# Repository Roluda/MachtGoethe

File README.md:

# MachtGoethe
Arduino Sketche und Schaltpläne für "Escape the Library"

Die Grundstruktur des Buches ist im Buch_Schaltplan.pdf abgebildet.

Mehr Details zu spezifischen Rätseln finden sich in den "schemes" Ordnern der Rätsel.

Die Sketche für die Arduinos sind in den "firmware" Ordnern zu finden.

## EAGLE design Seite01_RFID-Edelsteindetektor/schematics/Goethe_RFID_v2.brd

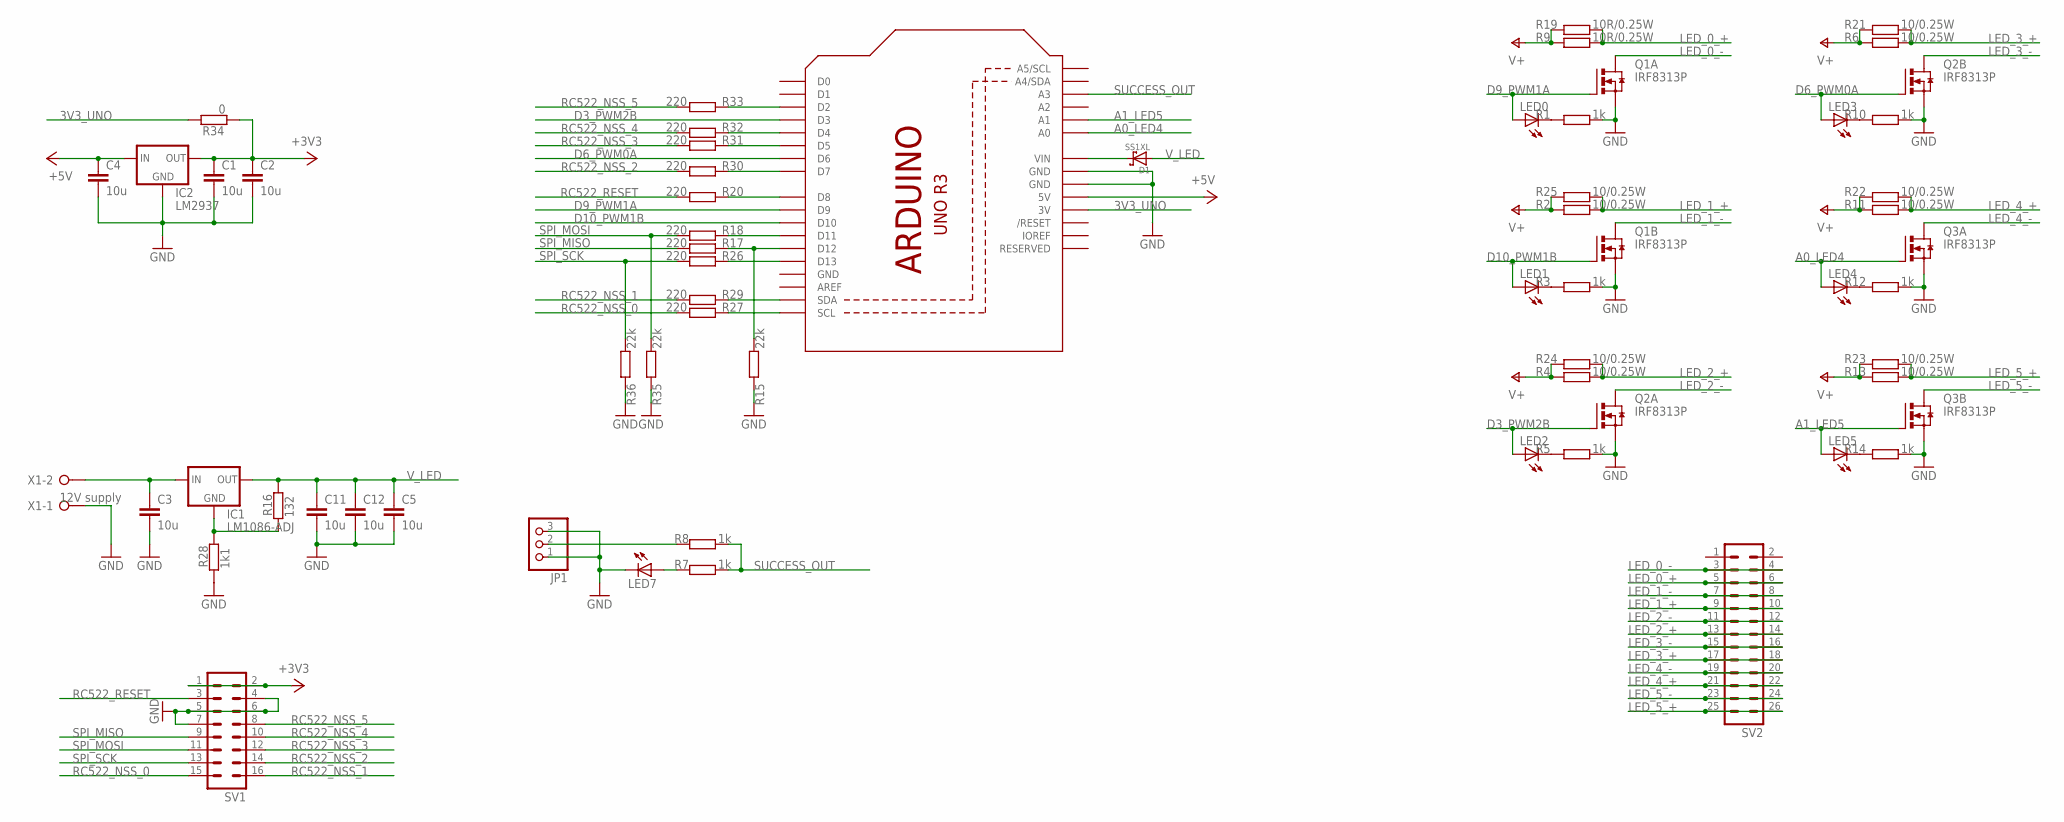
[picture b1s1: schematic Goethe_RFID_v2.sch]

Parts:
C1, C2, C3, C4, C5, C11, C12: 10u; C1206
D1: SS1XL; SUB_SMA
IC1: LM1086-ADJ; TO220L1
IC2: LM2937; SOT223
JP1: PINHD-1X3/90; 1X03/90
LED0, LED1, LED2, LED3, LED4, LED5, LED7: LED3MM
M1: ARDUINO_R3_SMALL; ARDUINOR3_SMALL
Q1, Q2, Q3: IRF8313P; SO-08
R1, R3, R5, R7, R8, R10, R12, R14: 1k; R0805
R2, R4, R6, R11, R13, R21, R22, R23, R24, R25: 10/0.25W; R0805
R9, R19: 10R/0.25W; R0805
R15, R35, R36: 22k; R0805
R16: 132; R0805
R17, R18, R20, R26, R27, R29, R30, R31, R32, R33: 220; R0805
R28: 1k1; R0805
R34: 0; R0805
SV1: ML16
SV2: ML26
X1: 12V supply; W237-132

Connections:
3V3_UNO: M1.3V, R34.1
+3V3: C1.1, C2.1, IC2.3 (OUT), R34.2, SV1.1, SV1.2
+5V: C4.1, IC2.1 (IN), M1.5V
A0_LED4: LED4.A, M1.A0, Q3.4 (G)
A1_LED5: LED5.A, M1.A1, Q3.2 (G)
D3_PWM2B: LED2.A, M1.D3, Q2.4 (G)
D6_PWM0A: LED3.A, M1.D6, Q2.2 (G)
D9_PWM1A: LED0.A, M1.D9, Q1.4 (G)
D10_PWM1B: LED1.A, M1.D10, Q1.2 (G)
GND: C1.2, C2.2, C3.2, C4.2, C5.2, C11.2, C12.2, IC2.2 (GND), JP1.1, JP1.3, LED7.K (C), M1.GND, M1.GND@1 (GND), M1.GND@2 (GND), Q1.1 (S), Q1.3 (S), Q2.1 (S), Q2.3 (S), Q3.1 (S), Q3.3 (S), R1.1, R3.1, R5.1, R10.1, R12.1, R14.1, R15.2, R28.2, R35.2, R36.2, SV1.4, SV1.5, SV1.6, SV1.7, X1.1
LED_0_+: R9.1, R19.1, SV2.5, SV2.6
LED_0_-: Q1.5 (D), Q1.6 (D), SV2.3, SV2.4
LED_1_+: R2.1, R25.1, SV2.9, SV2.10
LED_1_-: Q1.7 (D), Q1.8 (D), SV2.7, SV2.8
LED_2_+: R4.1, R24.1, SV2.13, SV2.14
LED_2_-: Q2.5 (D), Q2.6 (D), SV2.11, SV2.12
LED_3_+: R6.1, R21.1, SV2.17, SV2.18
LED_3_-: Q2.7 (D), Q2.8 (D), SV2.15, SV2.16
LED_4_+: R11.1, R22.1, SV2.21, SV2.22
LED_4_-: Q3.5 (D), Q3.6 (D), SV2.19, SV2.20
LED_5_+: R13.1, R23.1, SV2.25, SV2.26
LED_5_-: Q3.7 (D), Q3.8 (D), SV2.23, SV2.24
unnamed: LED1.K (C), R3.2
unnamed: M1.D12, R15.1, R17.2
unnamed: LED2.K (C), R5.2
unnamed: LED3.K (C), R10.2
unnamed: LED4.K (C), R12.2
unnamed: LED5.K (C), R14.2
unnamed: M1.D13, R26.2
unnamed: LED7.A, R7.2
unnamed: C3.1, IC1.3 (IN), X1.2
unnamed: LED0.K (C), R1.2
unnamed: IC1.1 (GND), R16.2, R28.1
unnamed: M1.D11, R18.2
unnamed: M1.D8, R20.2
unnamed: M1.SCL, R27.2
unnamed: M1.SDA, R29.2
unnamed: M1.D2, R33.2
unnamed: M1.D4, R32.2
unnamed: M1.D5, R31.2
unnamed: M1.D7, R30.2
unnamed: D1.C, M1.VIN
RC522_NSS_0: R27.1, SV1.15
RC522_NSS_1: R29.1, SV1.16
RC522_NSS_2: R30.1, SV1.14
RC522_NSS_3: R31.1, SV1.12
RC522_NSS_4: R32.1, SV1.10
RC522_NSS_5: R33.1, SV1.8
RC522_RESET: R20.1, SV1.3
SPI_MISO: R17.1, SV1.9
SPI_MOSI: R18.1, R35.1, SV1.11
SPI_SCK: R26.1, R36.1, SV1.13
SUCCESS_OUT: M1.A3, R7.1, R8.1
SUCCESS_OUT_: JP1.2, R8.2
V_LED: C5.1, C11.1, C12.1, D1.A, IC1.2 (OUT), R2.2, R4.2, R6.2, R9.2, R11.2, R13.2, R16.1, R19.2, R21.2, R22.2, R23.2, R24.2, R25.2

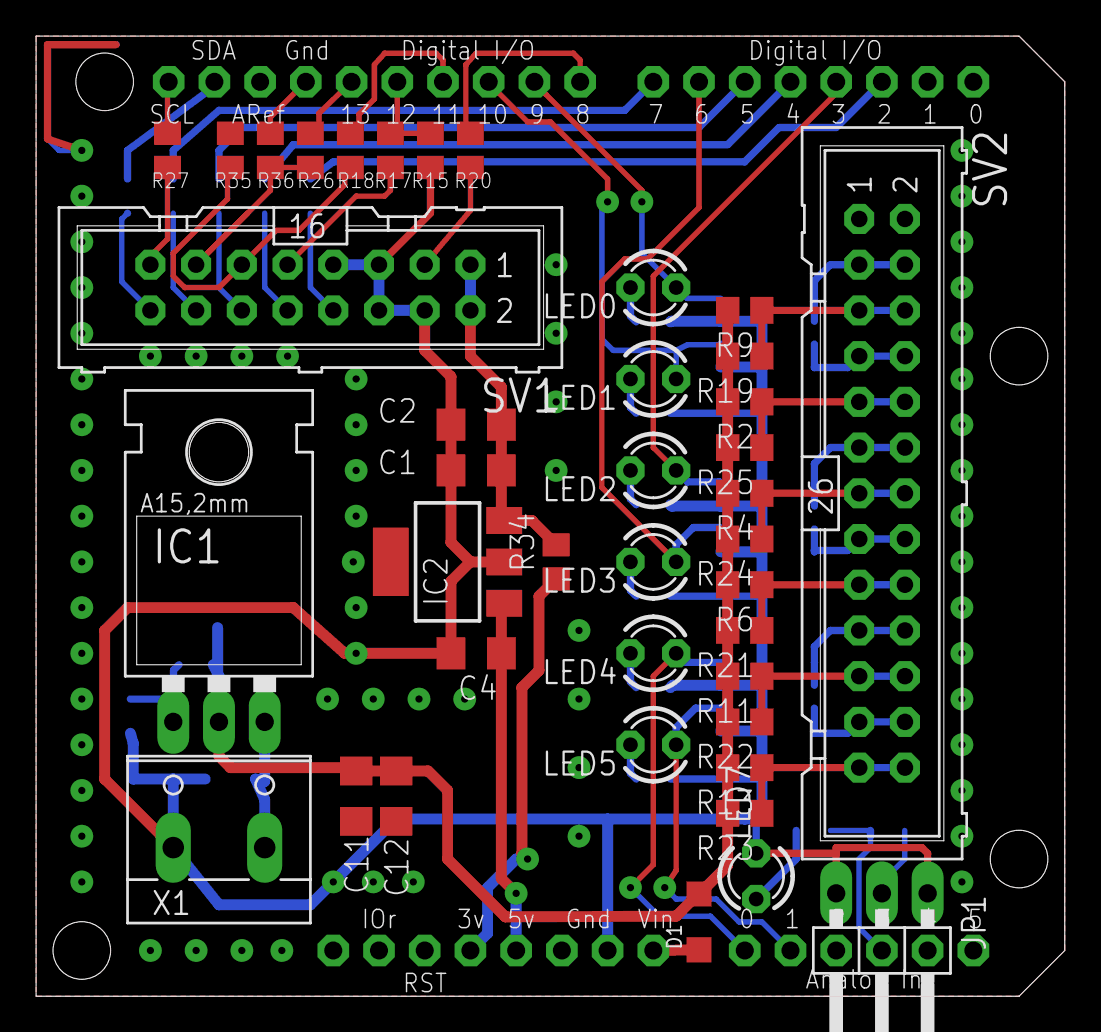
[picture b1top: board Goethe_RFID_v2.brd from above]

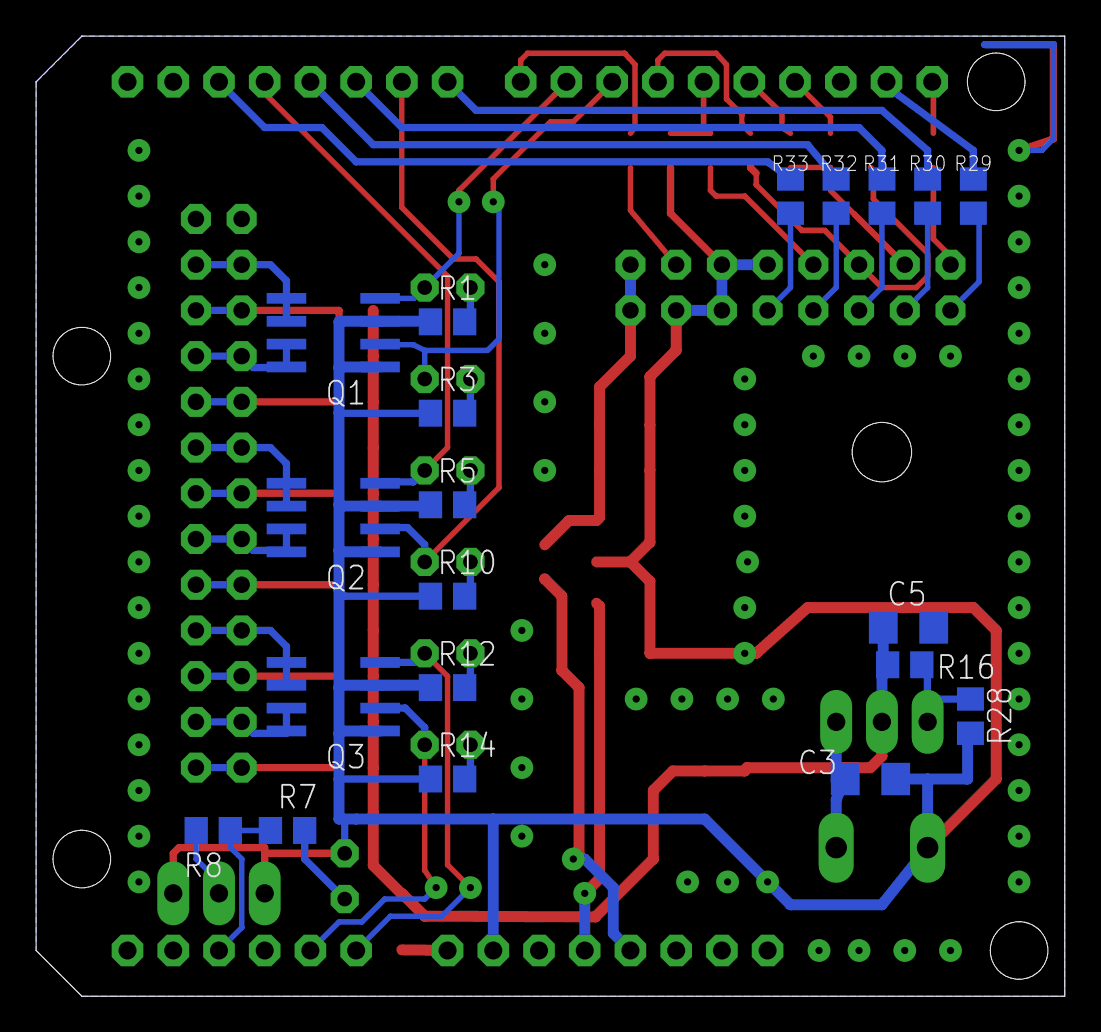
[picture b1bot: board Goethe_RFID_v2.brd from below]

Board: 2 copper layers, 57.1 x 53.3 mm, 61 parts (20 on the bottom side), 55 nets.

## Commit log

2019-11-17 Add muktiple Sketches for prototyping
2019-11-17 Added relais output to keypad code
2019-11-20 Added MelodieSketch
2019-11-20 Changed RFID_Prototype
    Not working
2019-11-20 Change Keypad to use only last four digits
2019-11-20 Add functionality for: electro magnets, win signal
2019-11-20 Add funtionality for magnet box
2019-11-20 Add: noise, openBox, receiveWin, releaseBigMagnet
2019-11-21 Add Stromfluss
2019-11-25 Changed Relais Outputs and pins
2019-11-26 Add support for box and locking magnet
2019-12-06 Working RFID detection with 6 readers
2019-12-16 Faster main-loop without hard-resetting the readers; Set LED outputs according to detected channels
2019-12-22 Test sketches for readers and LED
2019-12-22 Change control board to Arduino Uno; Add LED drivers
2020-01-15 Add LastStone Sketches
2020-01-15 Tweak Sketches
2020-01-16 Change SoundFIles To Play in Final
2020-01-17 New PCB for RFID controller
2020-01-17 Restructure Project
2020-01-17 Put Farbkreispuzzle into firmware folder
2020-01-17 Add scheme to Lopfpuzzle
2020-01-19 Add schemes for all puzzles
2020-01-26 Add RFID lib to repo; Adjust LED regulator voltage; Split RFID firmware in fron/back versions
2020-02-06 RFID detector firmware for new shield v2; Detector firmware for last page with learnable UID
2020-02-11 Individual gain settings for readers
2020-02-11 Fix missing wire on signal LED4
2020-02-11 Increase PWM frequency
2020-02-12 RGBA colors for backside LED
2020-02-12 Backlight blink colors adapted to actual front stone colors
2020-02-14 Touch detect: Make box open signal nonblocking
2020-02-14 Klopfpuzzle sensitivity adjust
2020-02-14 Change Touch Detect Polarity
2020-02-14 Steckpuzzle can reopen after cables were plugged out
2020-02-14 Remove Delay in loop
2020-02-28 Tweak everything
